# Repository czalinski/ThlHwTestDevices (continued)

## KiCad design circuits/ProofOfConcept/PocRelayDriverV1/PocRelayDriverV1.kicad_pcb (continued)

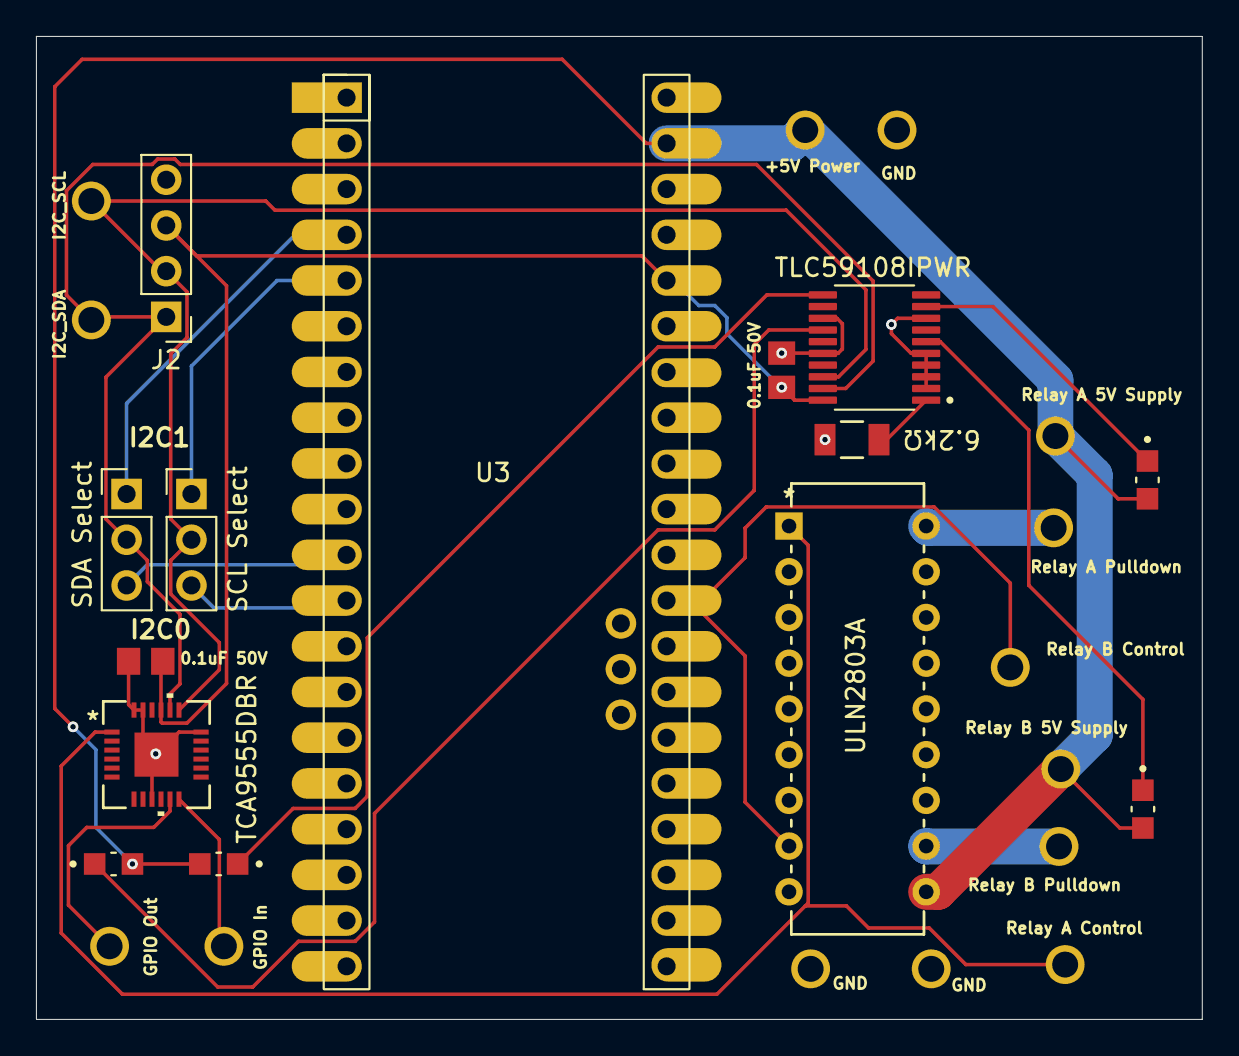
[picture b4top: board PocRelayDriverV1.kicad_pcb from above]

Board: 2 copper layers, 64.8 x 54.6 mm, 28 parts (0 on the bottom side), 20 nets.

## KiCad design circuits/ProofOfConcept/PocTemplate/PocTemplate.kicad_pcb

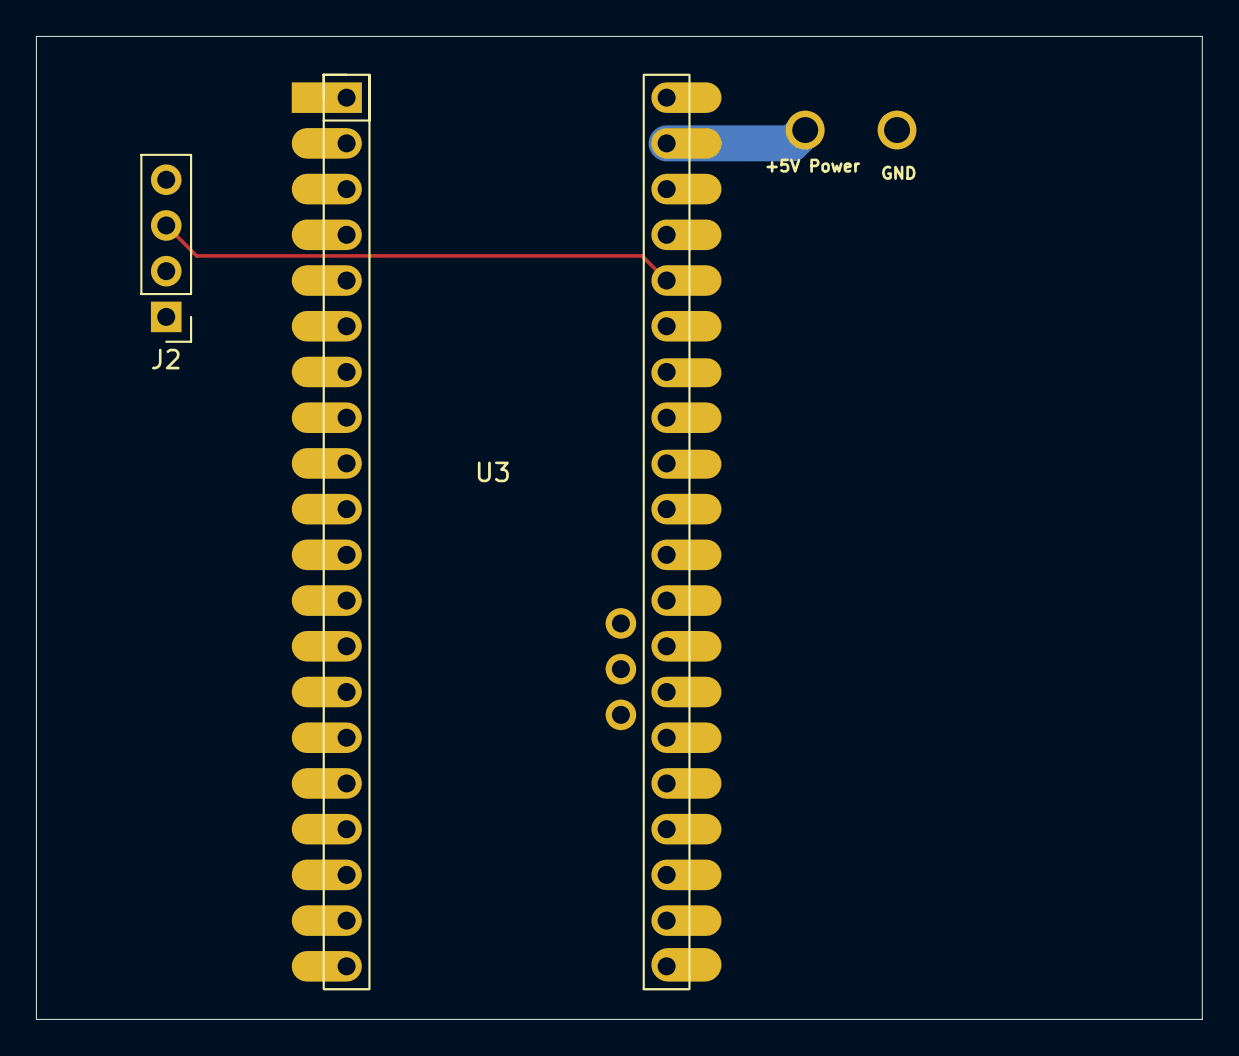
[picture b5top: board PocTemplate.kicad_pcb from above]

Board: 2 copper layers, 64.8 x 54.6 mm, 4 parts (0 on the bottom side), 3 nets.

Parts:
J2: OLED; PinHeader_1x04_P2.54mm_Vertical
TP1: +5V Power; KEYSTONE_4954
TP2: GND; KEYSTONE_4954
U3: WizNetPico_OnBoard

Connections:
+3.3V: J2.3, U3.36 (3V3)
+5V: TP1.TP, U3.39 (VSYS)
GND: J2.4, TP2.TP, U3.3 (GND), U3.8 (GND), U3.13 (GND), U3.18 (GND), U3.23 (GND), U3.28 (GND), U3.33 (AGND), U3.38 (GND), U3.42 (GND)

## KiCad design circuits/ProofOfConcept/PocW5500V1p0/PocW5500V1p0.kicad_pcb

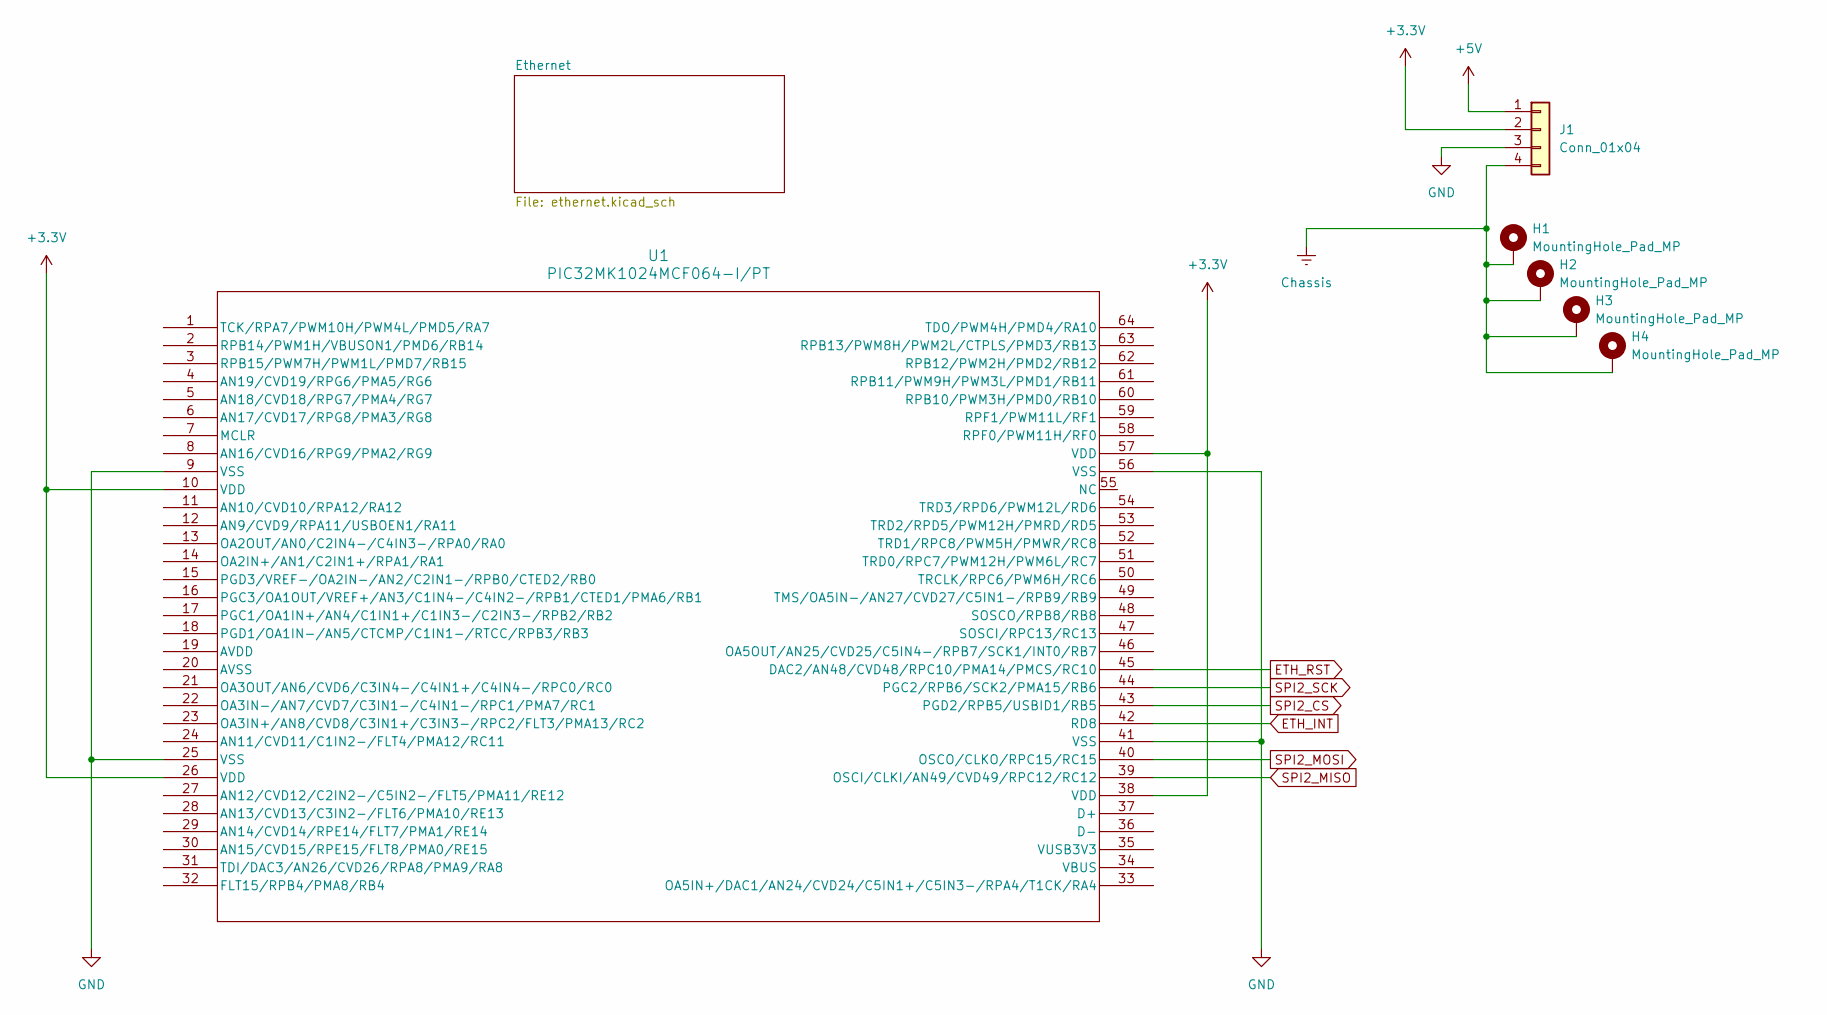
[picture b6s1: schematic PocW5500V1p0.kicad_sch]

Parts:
H1, H2, H3, H4: MountingHole_Pad_MP; MountingHole_3.2mm_M3_Pad_Via
J1: Conn_01x04; PinHeader_1x04_P2.54mm_Vertical
U1: PIC32MK1024MCF064-I/PT; PIC64_Breakout

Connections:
+3.3V: J1.2, U1.10 (VDD), U1.26 (VDD), U1.38 (VDD), U1.57 (VDD); also elsewhere on the board
+5V: J1.1
Chassis: H1.1 (MP_1), H2.1 (MP_1), H3.1 (MP_1), H4.1 (MP_1), J1.4; also elsewhere on the board
ETH_INT: U1.42 (RD8); also elsewhere on the board
ETH_RST: U1.45 (DAC2/AN48/CVD48/RPC10/PMA14/PMCS/RC10); also elsewhere on the board
GND: J1.3, U1.9 (VSS), U1.25 (VSS), U1.41 (VSS), U1.56 (VSS); also elsewhere on the board
SPI2_CS: U1.43 (PGD2/RPB5/USBID1/RB5); also elsewhere on the board
SPI2_MISO: U1.39 (OSCI/CLKI/AN49/CVD49/RPC12/RC12); also elsewhere on the board
SPI2_MOSI: U1.40 (OSCO/CLKO/RPC15/RC15); also elsewhere on the board
SPI2_SCK: U1.44 (PGC2/RPB6/SCK2/PMA15/RB6); also elsewhere on the board

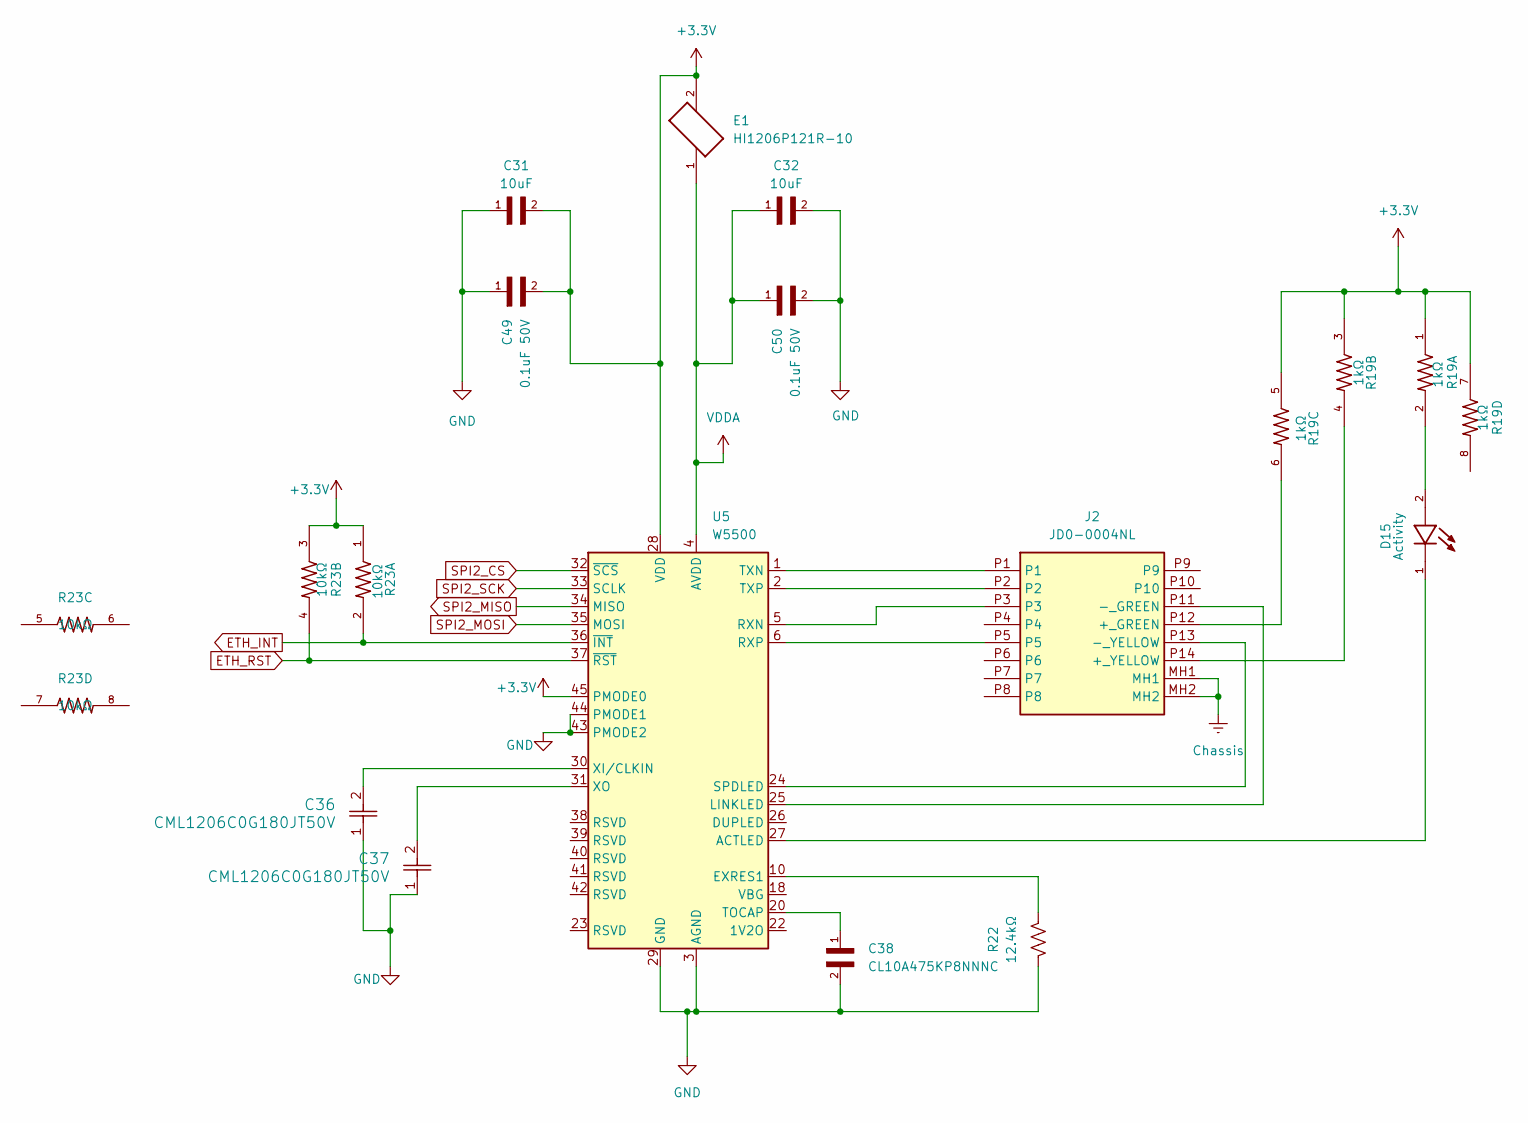
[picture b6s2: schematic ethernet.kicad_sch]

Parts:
C31, C32: 10uF; CAPC3216X180N
C36, C37: CML1206C0G180JT50V; CAP_CML_1206_.3-8200PF_STP
C38: CL10A475KP8NNNC; CAPC1608X90N
C49, C50: 0.1uF 50V; CAPC2012X70
D15: Activity; LED_LTST-C170GKT; PARTREV I
E1: HI1206P121R-10; FB_HI1206P121R-10
J2: JD0-0004NL; JD00004NL; Manufacturer_Part_Number JD0-0004NL; Mouser Part Number 673-JD0-0004NL
R19: 1kΩ; RESCAV80P320X160X70-8N
R22: 12.4kΩ; RES_1206
R23: 10kΩ; RESCAV80P320X160X70-8N
U5: W5500; LQFP-48_7x7mm_P0.5mm

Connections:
+3.3V: C31.2, C49.2, E1.2, R19.1, R19.3, R19.5, R19.7, R23.1, R23.3, U5.28 (VDD), U5.45 (PMODE0); also elsewhere on the board
Chassis: J2.MH1, J2.MH2; also elsewhere on the board
ETH_INT: R23.2, U5.36 (~INT); also elsewhere on the board
ETH_RST: R23.4, U5.37 (~RST); also elsewhere on the board
GND: C31.1, C32.2, C36.1, C37.1, C38.2, C49.1, C50.2, R22.2, U5.3 (AGND), U5.9 (AGND), U5.14 (AGND), U5.16 (AGND), U5.19 (AGND), U5.29 (GND), U5.43 (PMODE2), U5.44 (PMODE1), U5.48 (AGND); also elsewhere on the board
unnamed: D15.2, R19.2
unnamed: J2.P12 (+_GREEN), R19.6
unnamed: J2.P14 (+_YELLOW), R19.4
unnamed: J2.P11 (-_GREEN), U5.25 (LINKLED)
unnamed: J2.P13 (-_YELLOW), U5.24 (SPDLED)
unnamed: D15.1, U5.27 (ACTLED)
unnamed: R22.1, U5.10 (EXRES1)
unnamed: J2.P3, U5.5 (RXN)
unnamed: J2.P5, U5.6 (RXP)
unnamed: C38.1, U5.20 (TOCAP)
unnamed: J2.P1, U5.1 (TXN)
unnamed: J2.P2, U5.2 (TXP)
unnamed: C36.2, U5.30 (XI/CLKIN)
unnamed: C37.2, U5.31 (XO)
SPI2_CS: U5.32 (~SCS); also elsewhere on the board
SPI2_MISO: U5.34 (MISO); also elsewhere on the board
SPI2_MOSI: U5.35 (MOSI); also elsewhere on the board
SPI2_SCK: U5.33 (SCLK); also elsewhere on the board
VDDA: C32.1, C50.1, E1.1, U5.4 (AVDD), U5.8 (AVDD), U5.11 (AVDD), U5.15 (AVDD), U5.17 (AVDD), U5.21 (AVDD)

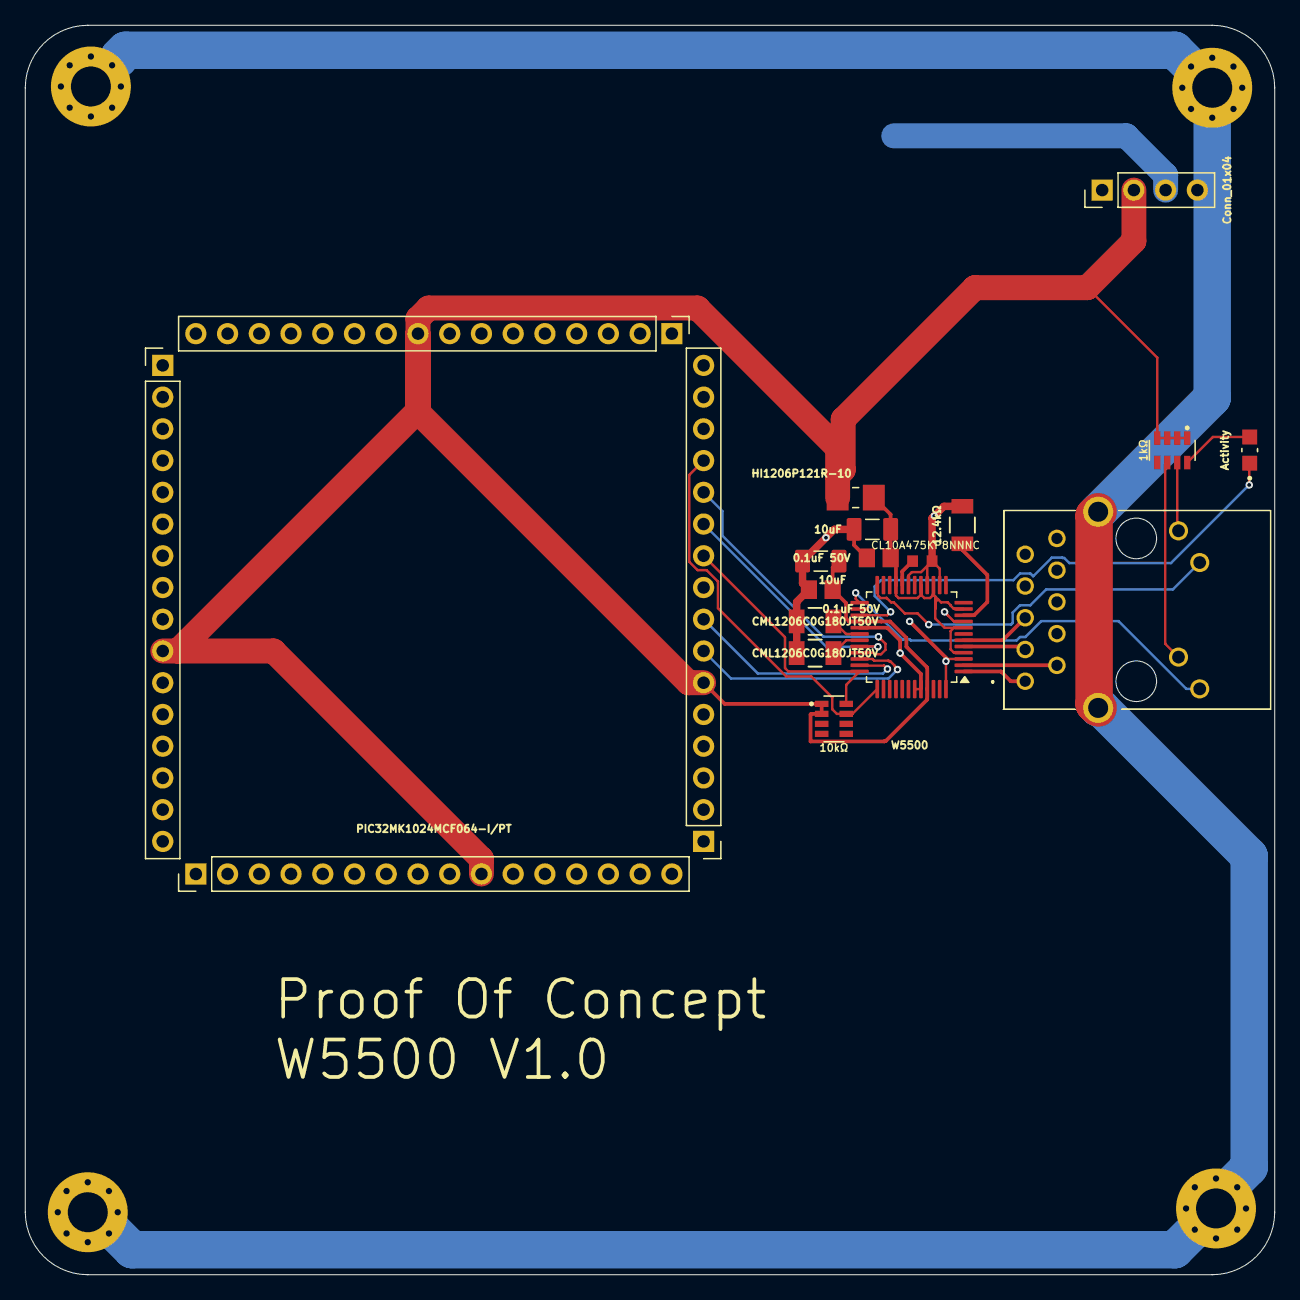
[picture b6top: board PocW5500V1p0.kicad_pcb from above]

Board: 2 copper layers, 100.0 x 100.0 mm, 20 parts (0 on the bottom side), 24 nets.
